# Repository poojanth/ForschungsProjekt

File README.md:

## ForschungsProjekt

KiCad PCB Design for an Implantable Optical Sensor System for Glioblastoma Cancer Patients

## Overview

This project focused on the design and optimization of a printed circuit board (PCB) for an implantable optical sensor system intended for biomedical research. The system concept is based on fluorescence detection for monitoring possible glioblastoma recurrence after tumor resection.

The implant concept consists of two main parts:

* **Sensor Unit** - responsible for fluorescence excitation and detection.
* **Control Unit** - responsible for power management, signal handling, and system control.

The aim of the project was to improve the electrical design, component selection, PCB layout, compactness, and feasibility of the optical implant system.

---

## My Contribution

* Researched requirements for implantable optical sensor systems
* Compared suitable electronic components for the device
* Investigated power management options for implantable medical devices
* Designed PCB layouts for the sensor unit and control unit using KiCad
* Considered compactness, signal integrity, power/ground planes, and routing rules
* Evaluated an alternative two-step placement approach for improved clinical feasibility

---

## Key Design Considerations

* Fluorescence excitation using UV/blue LEDs
* Fluorescence detection using photodiodes
* Compact PCB layout for implantable use
* Power-efficient component selection
* Separate power and ground planes for improved signal integrity
* MRI compatibility and biocompatibility considerations
* Sensor and control-unit separation for better placement flexibility

---

## Tools Used

* KiCad
* PCB schematic design
* PCB layout design
* Component datasheet analysis
* Literature research

---

## Skills Demonstrated

* PCB design
* Biomedical hardware design
* KiCad workflow
* Component selection
* Power management research
* Sensor system design
* Implantable medical device considerations
* Technical documentation

---

## Repository Structure

```text
.
├── KiCad_Project/
│   ├── project_file.kicad_pro
│   ├── schematic.kicad_sch
│   └── pcb_layout.kicad_pcb
│
├── Docs/
│   ├── schematic.pdf
│   ├── pcb_layout_images/
│   └── 3d_pcb_views/
│
├── README.md
└── .gitignore
```

---

## Project Status

This project represents a research and design-stage PCB development work. The PCB layout and component selection were completed as part of the research project. Experimental validation and hardware testing were identified as future work.

---

## Confidentiality Note

This repository contains only a non-confidential project overview and selected design documentation. Sensitive institutional material, unpublished restricted details, and confidential research data are not included.

---

## Author

**Poojan Thakar**
M.Sc. Medical Systems Engineering
Otto von Guericke University Magdeburg

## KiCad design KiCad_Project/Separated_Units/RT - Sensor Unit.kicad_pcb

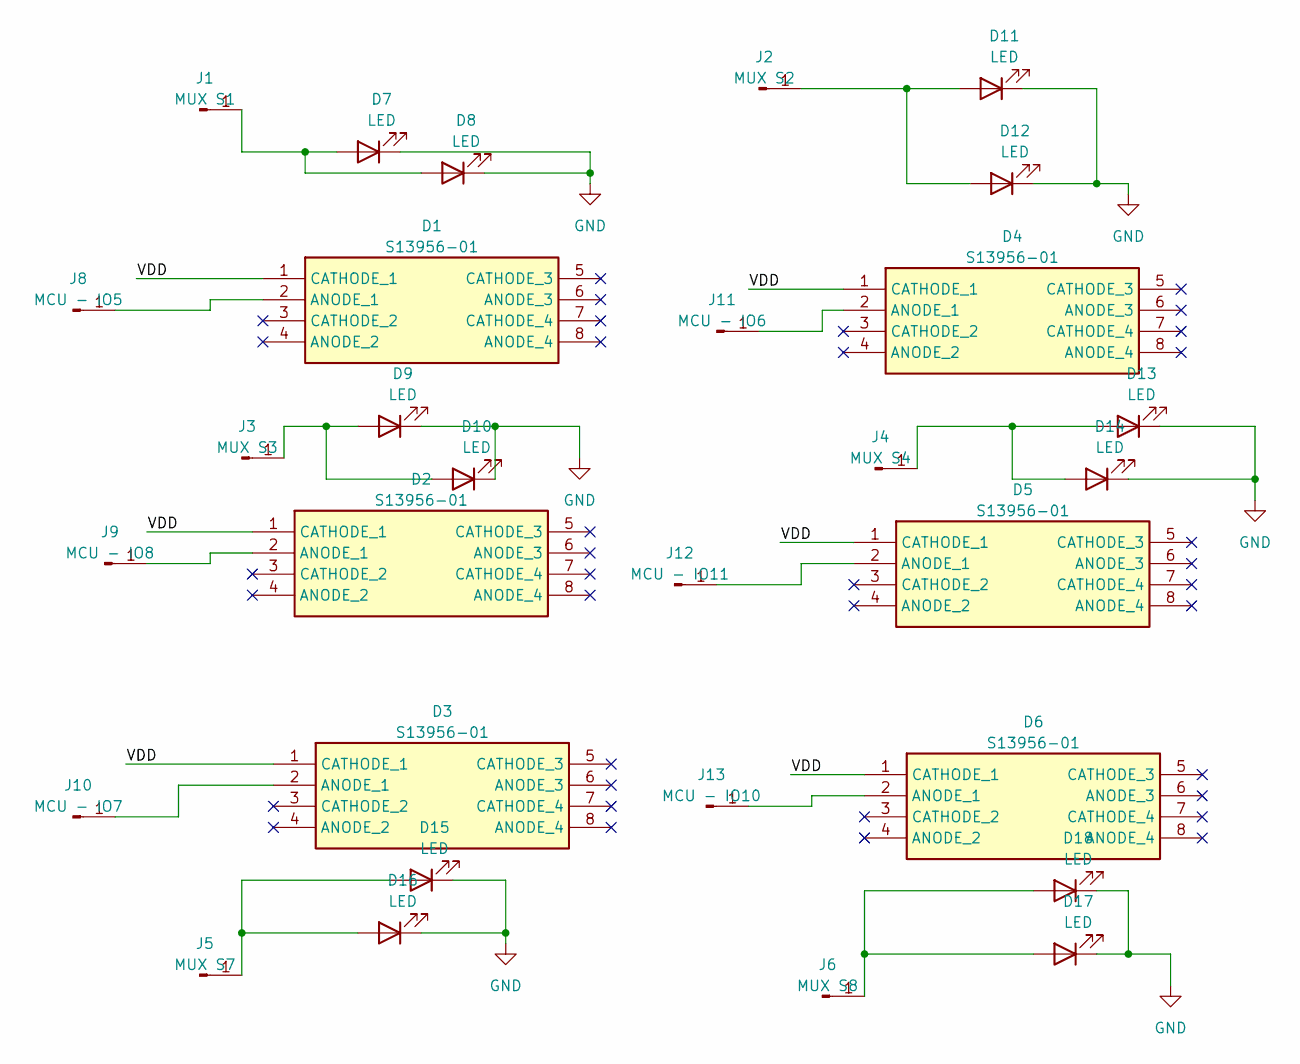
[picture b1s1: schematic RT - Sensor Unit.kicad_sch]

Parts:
D1, D2, D3, D4, D5, D6: S13956-01; S1395601; Manufacturer_Part_Number S13956-01
D7, D8, D9, D10, D11, D12, D13, D14, D15, D16, D17, D18: LED; LED_0201_0603Metric_Pad0.64x0.40mm_HandSolder
J1: MUX S1; PinHeader_1x01_P1.00mm_Vertical
J2: MUX S2; PinHeader_1x01_P1.00mm_Vertical
J3: MUX S3; PinHeader_1x01_P1.00mm_Vertical
J4: MUX S4; PinHeader_1x01_P1.00mm_Vertical
J5: MUX S7; PinHeader_1x01_P1.00mm_Vertical
J6: MUX S8; PinHeader_1x01_P1.00mm_Vertical
J8: MCU - IO5; PinHeader_1x01_P1.00mm_Vertical
J9: MCU - IO8; PinHeader_1x01_P1.00mm_Vertical
J10: MCU - IO7; PinHeader_1x01_P1.00mm_Vertical
J11: MCU - IO6; PinHeader_1x01_P1.00mm_Vertical
J12: MCU - IO11; PinHeader_1x01_P1.00mm_Vertical
J13: MCU - IO10; PinHeader_1x01_P1.00mm_Vertical

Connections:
/VDD: D1.1 (CATHODE_1), D2.1 (CATHODE_1), D3.1 (CATHODE_1), D4.1 (CATHODE_1), D5.1 (CATHODE_1), D6.1 (CATHODE_1)
GND: D7.1 (K), D8.1 (K), D9.1 (K), D10.1 (K), D11.1 (K), D12.1 (K), D13.1 (K), D14.1 (K), D15.1 (K), D16.1 (K), D17.1 (K), D18.1 (K)
unnamed: D1.2 (ANODE_1), J8.1
unnamed: D2.2 (ANODE_1), J9.1
unnamed: D3.2 (ANODE_1), J10.1
unnamed: D4.2 (ANODE_1), J11.1
unnamed: D5.2 (ANODE_1), J12.1
unnamed: D6.2 (ANODE_1), J13.1
unnamed: D7.2 (A), D8.2 (A), J1.1
unnamed: D9.2 (A), D10.2 (A), J3.1
unnamed: D11.2 (A), D12.2 (A), J2.1
unnamed: D13.2 (A), D14.2 (A), J4.1
unnamed: D15.2 (A), D16.2 (A), J5.1
unnamed: D17.2 (A), D18.2 (A), J6.1

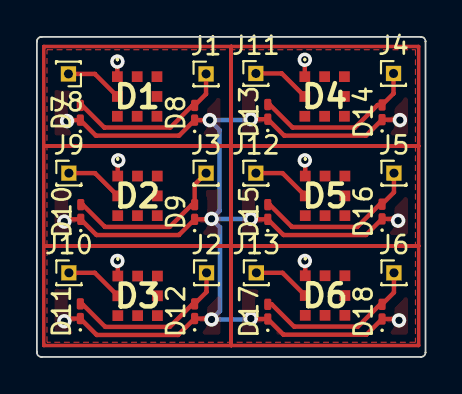
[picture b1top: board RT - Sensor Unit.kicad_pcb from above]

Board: 2 copper layers, 21.6 x 17.8 mm, 30 parts (0 on the bottom side), 14 nets.

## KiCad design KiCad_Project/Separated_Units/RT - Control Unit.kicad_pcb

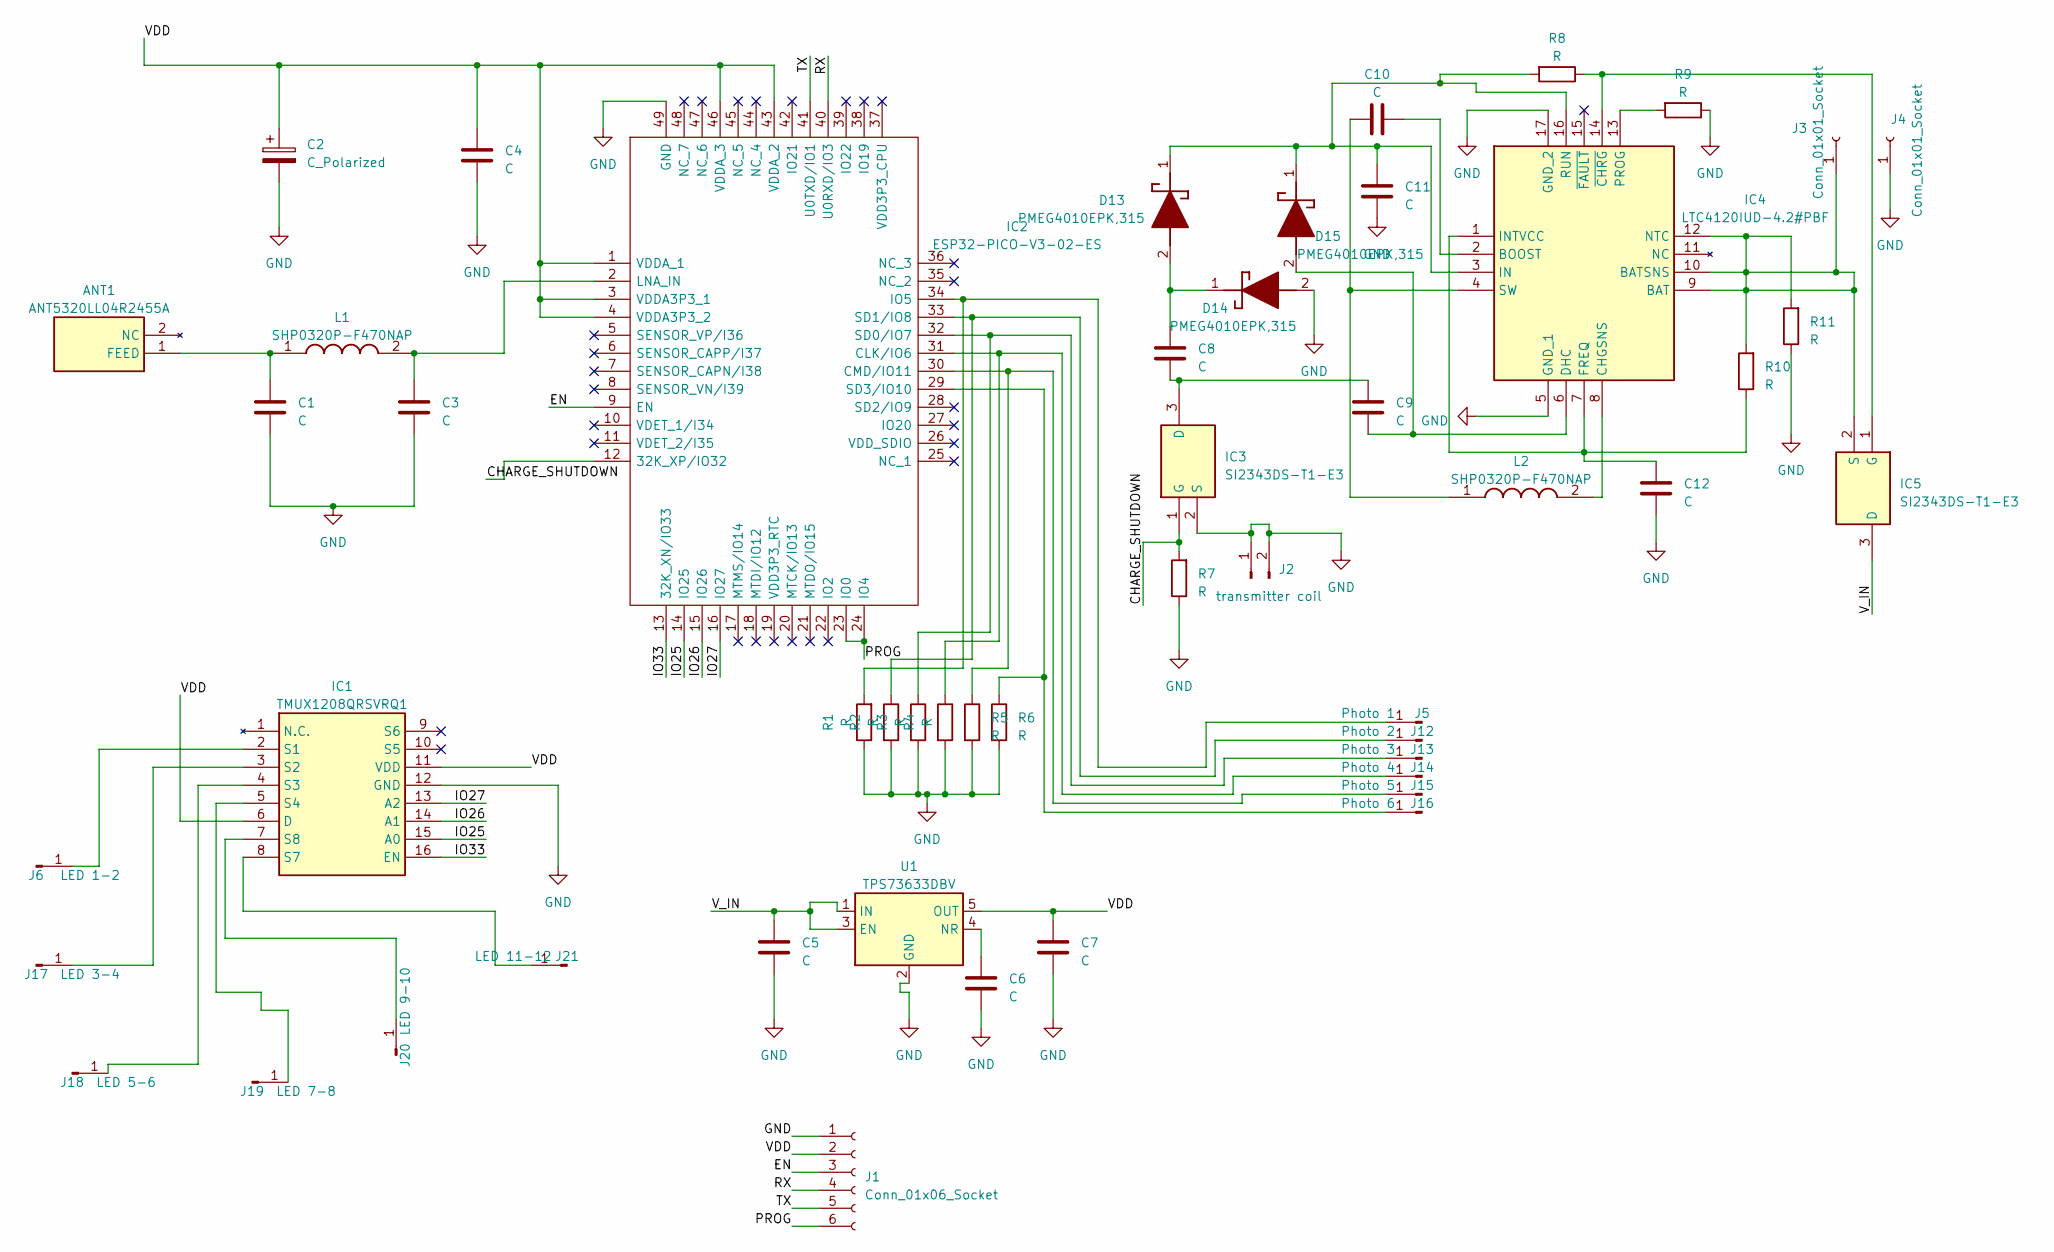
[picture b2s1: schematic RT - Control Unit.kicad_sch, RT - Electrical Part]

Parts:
ANT1: ANT5320LL04R2455A; ANTC5320X170N; Manufacturer_Part_Number ANT5320LL04R2455A; Mouser Part Number 603-ANT5320LL04R2455
C1, C3, C4, C5, C6, C7, C8, C9, C10, C11, C12: C; C_0603_1608Metric_Pad1.08x0.95mm_HandSolder
C2: C_Polarized; C_0603_1608Metric_Pad1.08x0.95mm_HandSolder
D13, D14, D15: PMEG4010EPK,315; PMEG4010EPK315; Manufacturer_Part_Number PMEG4010EPK,315; Mouser Part Number 771-PMEG4010EPK,315
IC1: TMUX1208QRSVRQ1; Manufacturer_Part_Number TMUX1208QRSVRQ1; Mouser Part Number 595-TMUX1208QRSVRQ1
IC2: ESP32-PICO-V3-02-ES; ESP32PICOV302ES; Manufacturer_Part_Number ESP32-PICO-V3-02-ES
IC3, IC5: SI2343DS-T1-E3; SOT95P237X112-3N; Manufacturer_Part_Number SI2343DS-T1-E3; Mouser Part Number 781-SI2343DS-T1-E3
IC4: LTC4120IUD-4.2#PBF; QFN50P300X300X80-17N-D; Manufacturer_Part_Number LTC4120IUD-4.2#PBF; Mouser Part Number 584-C4120IUD-4.2PBF
J1: Conn_01x06_Socket; PinHeader_2x03_P1.00mm_Vertical
J2: transmitter coil; PinHeader_1x02_P1.00mm_Vertical
J3, J4: Conn_01x01_Socket; PinHeader_1x01_P2.54mm_Vertical
J5: Photo 1; PinHeader_1x01_P1.00mm_Vertical
J6: LED 1-2; PinHeader_1x01_P1.00mm_Vertical
J12: Photo 2; PinHeader_1x01_P1.00mm_Vertical
J13: Photo 3; PinHeader_1x01_P1.00mm_Vertical
J14: Photo 4; PinHeader_1x01_P1.00mm_Vertical
J15: Photo 5; PinHeader_1x01_P1.00mm_Vertical
J16: Photo 6; PinHeader_1x01_P1.00mm_Vertical
J17: LED 3-4; PinHeader_1x01_P1.00mm_Vertical
J18: LED 5-6; PinHeader_1x01_P1.00mm_Vertical
J19: LED 7-8; PinHeader_1x01_P1.00mm_Vertical
J20: LED 9-10; PinHeader_1x01_P1.00mm_Vertical
J21: LED 11-12; PinHeader_1x01_P1.00mm_Vertical
L1, L2: SHP0320P-F470NAP; SHP0320PF470NAP; Manufacturer_Part_Number SHP0320P-F470NAP
R1, R2, R3, R4, R5, R6, R7, R8, R9, R10, R11: R; R_0402_1005Metric_Pad0.72x0.64mm_HandSolder
U1: TPS73633DBV; SOT-23-5

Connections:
/CHARGE_SHUTDOWN: IC2.12 (32K_XP/IO32), IC3.1 (G), R7.2
/EN: IC2.9 (EN), J1.3
/IO25: IC1.15 (A0), IC2.14 (IO25)
/IO26: IC1.14 (A1), IC2.15 (IO26)
/IO27: IC1.13 (A2), IC2.16 (IO27)
/IO33: IC1.16 (EN), IC2.13 (32K_XN/IO33)
/PROG: IC2.23 (IO0), IC2.24 (IO4), J1.6
/RX: IC2.40 (U0RXD/IO3), J1.4
/TX: IC2.41 (U0TXD/IO1), J1.5
/VDD: C2.1, C4.1, C7.1, IC1.6 (D), IC1.11 (VDD), IC2.1 (VDDA_1), IC2.3 (VDDA3P3_1), IC2.4 (VDDA3P3_2), IC2.43 (VDDA_2), IC2.46 (VDDA_3), J1.2, U1.5 (OUT)
/V_IN: C5.1, IC5.3 (D), U1.1 (IN), U1.3 (EN)
GND: C1.2, C2.2, C3.2, C4.2, C5.2, C6.2, C7.2, C11.2, C12.1, D14.2 (A), IC1.12 (GND), IC2.49 (GND), IC3.2 (S), IC4.5 (GND_1), IC4.17 (GND_2), J1.1, J4.1, R1.1, R2.2, R3.2, R4.2, R5.2, R6.2, R7.1, R9.1, R11.1, U1.2 (GND)
unnamed: ANT1.1 (FEED), C1.1, L1.1
unnamed: C8.1, D13.2 (A), D14.1 (K)
unnamed: C11.1, D13.1 (K), D15.1 (K), IC4.3 (IN), IC4.16 (RUN), R8.2
unnamed: C9.1, D15.2 (A), IC4.6 (DHC)
unnamed: IC1.2 (S1), J6.1
unnamed: IC1.3 (S2), J17.1
unnamed: IC1.4 (S3), J18.1
unnamed: IC1.5 (S4), J19.1
unnamed: IC1.8 (S7), J21.1
unnamed: IC1.7 (S8), J20.1
unnamed: IC2.31 (CLK/IO6), J14.1, R4.1
unnamed: IC2.30 (CMD/IO11), J15.1, R5.1
unnamed: IC2.34 (IO5), J5.1, R1.2
unnamed: C3.1, IC2.2 (LNA_IN), L1.2
unnamed: IC2.32 (SD0/IO7), J13.1, R3.1
unnamed: IC2.33 (SD1/IO8), J12.1, R2.1
unnamed: IC2.29 (SD3/IO10), J16.1, R6.1
unnamed: C8.2, C9.2, IC3.3 (D)
unnamed: IC4.9 (BAT), IC4.10 (BATSNS), IC4.12 (NTC), IC5.2 (S), J3.1, R10.2, R11.2
unnamed: C10.2, IC4.2 (BOOST)
unnamed: IC4.8 (CHGSNS), L2.2
unnamed: C12.2, IC4.1 (INTVCC), IC4.7 (FREQ), R10.1
unnamed: IC4.13 (PROG), R9.2
unnamed: C10.1, IC4.4 (SW), L2.1
unnamed: IC4.14 (~CHRG), IC5.1 (G), R8.1
unnamed: C6.1, U1.4 (NR)

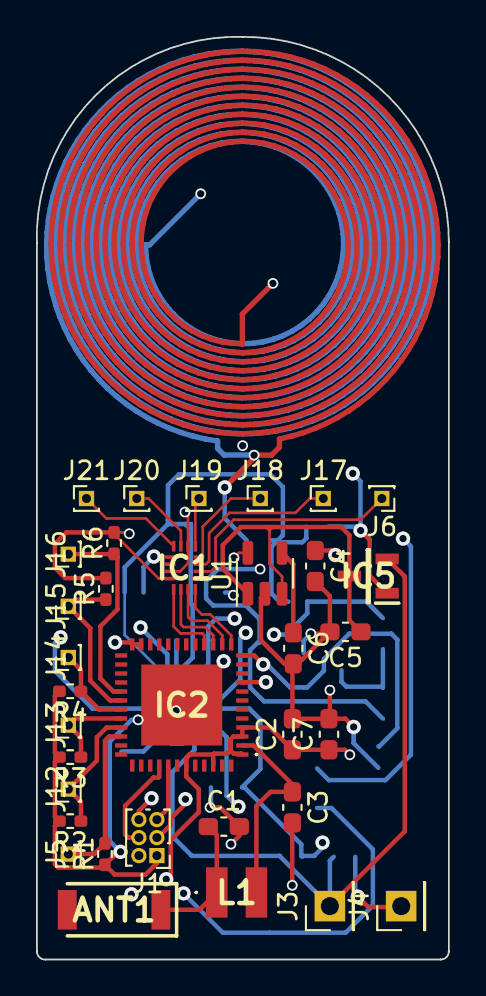
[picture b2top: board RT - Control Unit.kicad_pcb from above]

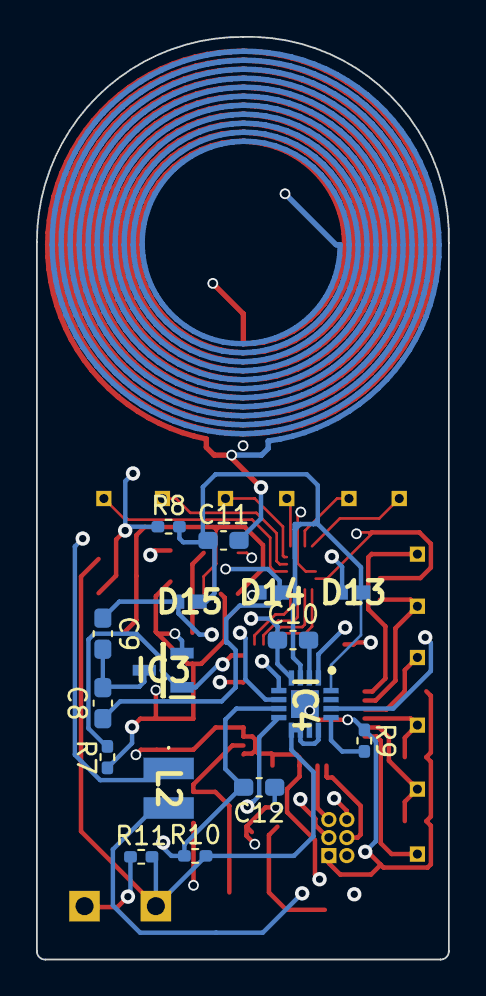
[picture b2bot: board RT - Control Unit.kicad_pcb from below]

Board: 4 copper layers, 22.9 x 51.3 mm, 50 parts (16 on the bottom side), 38 nets.

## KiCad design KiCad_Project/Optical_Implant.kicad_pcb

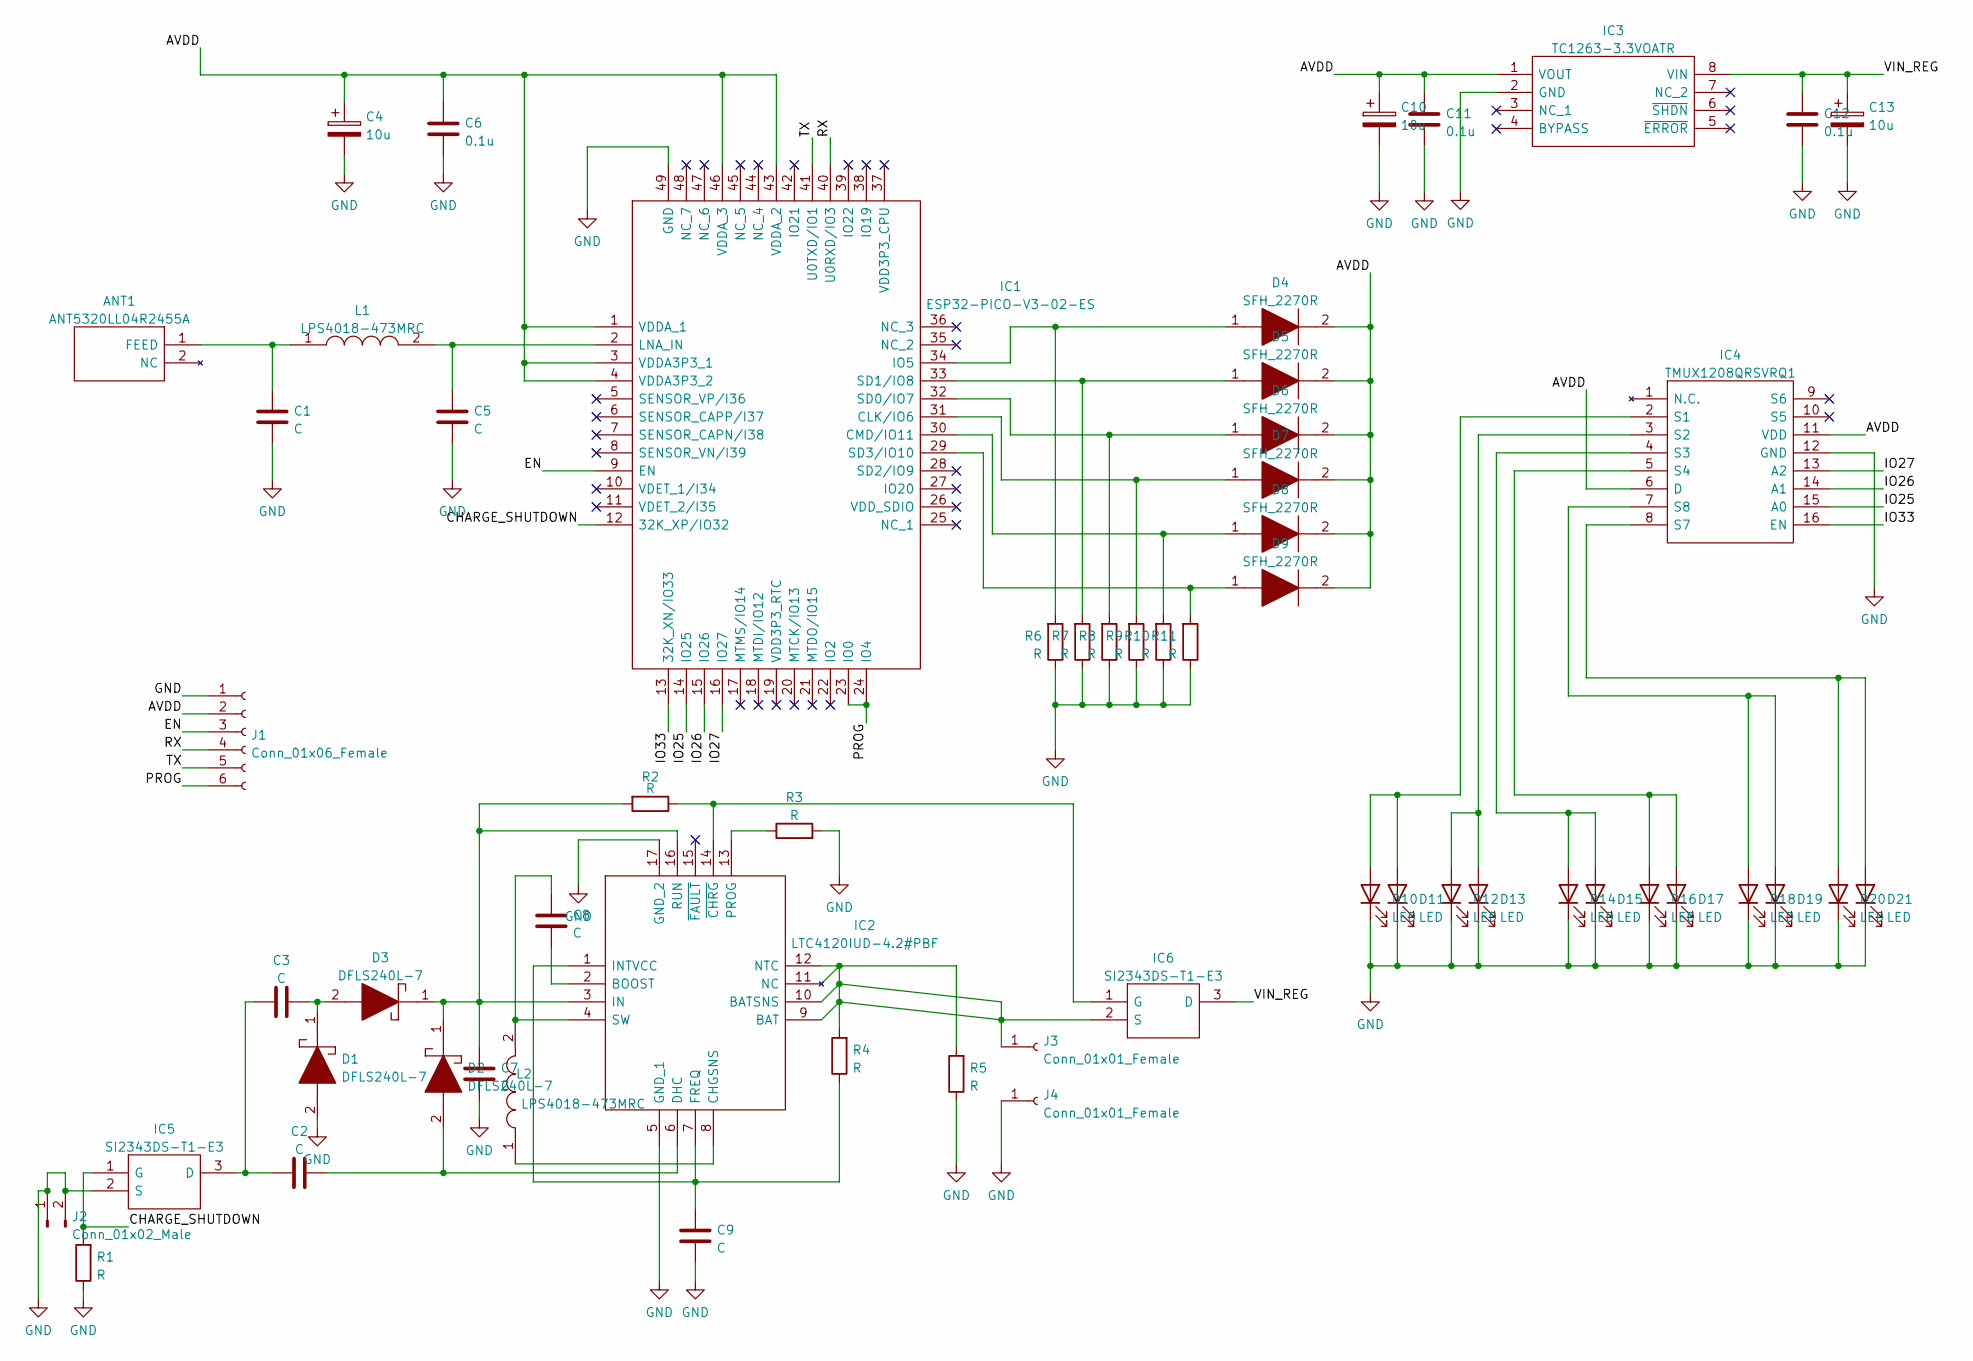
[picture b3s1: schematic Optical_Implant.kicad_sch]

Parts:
ANT1: ANT5320LL04R2455A; ANTC5320X170N; Mouser Part Number 603-ANT5320LL04R2455
C1, C2, C3, C5, C7, C8, C9: C; C_0603_1608Metric_Pad1.08x0.95mm_HandSolder
C4, C10, C13: 10u; C_0603_1608Metric_Pad1.08x0.95mm_HandSolder
C6, C11, C12: 0.1u; C_0603_1608Metric_Pad1.08x0.95mm_HandSolder
D1, D2, D3: DFLS240L-7; DFLS240L7; Manufacturer_Part_Number DFLS240L-7; Mouser Part Number 621-DFLS240L-7
D4, D5, D6, D7, D8, D9: SFH_2270R; SFH2270R; Mouser Part Number 720-SFH2270R
D10, D11, D12, D13, D14, D15, D16, D17, D18, D19, D20, D21: LED; LED_0603_1608Metric_Pad1.05x0.95mm_HandSolder
IC1: ESP32-PICO-V3-02-ES; ESP32PICOV302ES; Manufacturer_Part_Number ESP32-PICO-V3-02-ES
IC2: LTC4120IUD-4.2#PBF; QFN50P300X300X80-17N-D; Mouser Part Number 584-C4120IUD-4.2PBF
IC3: TC1263-3.3VOATR; SOIC127P600X175-8N; Mouser Part Number 579-TC1263-3.3VOATR
IC4: TMUX1208QRSVRQ1; Mouser Part Number 595-TMUX1208QRSVRQ1
IC5, IC6: SI2343DS-T1-E3; SOT95P237X112-3N; Mouser Part Number 781-SI2343DS-T1-E3
J1: Conn_01x06_Female; PinHeader_2x03_P1.00mm_Vertical
J2: Conn_01x02_Male; PinHeader_1x02_P2.54mm_Vertical
J3, J4: Conn_01x01_Female; PinHeader_1x01_P2.54mm_Vertical
L1: LPS4018-473MRC; L_0603_1608Metric_Pad1.05x0.95mm_HandSolder; Manufacturer_Part_Number LPS4018-473MRC; Mouser Part Number 994-LPS4018-473MRC
L2: LPS4018-473MRC; LPS4018473MRC; Manufacturer_Part_Number LPS4018-473MRC; Mouser Part Number 994-LPS4018-473MRC
R1, R2, R3, R4, R5, R6, R7, R8, R9, R10, R11: R; R_0402_1005Metric_Pad0.72x0.64mm_HandSolder

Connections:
/AVDD: C4.1, C6.1, C10.1, C11.1, D4.2, D5.2, D6.2, D7.2, D8.2, D9.2, IC1.1 (VDDA_1), IC1.3 (VDDA3P3_1), IC1.4 (VDDA3P3_2), IC1.43 (VDDA_2), IC1.46 (VDDA_3), IC3.1 (VOUT), IC4.6 (D), IC4.11 (VDD), J1.2
/CHARGE_SHUTDOWN: IC1.12 (32K_XP/IO32), IC5.1 (G), R1.2
/EN: IC1.9 (EN), J1.3
/IO25: IC1.14 (IO25), IC4.15 (A0)
/IO26: IC1.15 (IO26), IC4.14 (A1)
/IO27: IC1.16 (IO27), IC4.13 (A2)
/IO33: IC1.13 (32K_XN/IO33), IC4.16 (EN)
/PROG: IC1.23 (IO0), IC1.24 (IO4), J1.6
/RX: IC1.40 (U0RXD/IO3), J1.4
/TX: IC1.41 (U0TXD/IO1), J1.5
/VIN_REG: C12.1, C13.1, IC3.8 (VIN), IC6.3 (D)
GND: C1.2, C4.2, C5.2, C6.2, C7.2, C9.2, C10.2, C11.2, C12.2, C13.2, D1.2, D10.1 (K), D11.1 (K), D12.1 (K), D13.1 (K), D14.1 (K), D15.1 (K), D16.1 (K), D17.1 (K), D18.1 (K), D19.1 (K), D20.1 (K), D21.1 (K), IC1.49 (GND), IC2.5 (GND_1), IC2.17 (GND_2), IC3.2 (GND), IC4.12 (GND), IC5.2 (S), J1.1, J2.1, J2.2, J4.1, R1.1, R3.2, R5.1, R6.1, R7.1, R8.1, R9.1, R10.1, R11.1
unnamed: ANT1.1 (FEED), C1.1, L1.1
unnamed: C2.1, C3.1, IC5.3 (D)
unnamed: C2.2, D2.2, IC2.6 (DHC)
unnamed: C3.2, D1.1, D3.2
unnamed: C5.1, IC1.2 (LNA_IN), L1.2
unnamed: C7.1, D2.1, D3.1, IC2.3 (IN), IC2.16 (RUN), R2.2
unnamed: C8.1, IC2.4 (SW), L2.2
unnamed: C8.2, IC2.2 (BOOST)
unnamed: C9.1, IC2.1 (INTVCC), IC2.7 (FREQ), R4.1
unnamed: D4.1, IC1.34 (IO5), R6.2
unnamed: D5.1, IC1.33 (SD1/IO8), R7.2
unnamed: D6.1, IC1.32 (SD0/IO7), R8.2
unnamed: D7.1, IC1.31 (CLK/IO6), R9.2
unnamed: D8.1, IC1.30 (CMD/IO11), R10.2
unnamed: D9.1, IC1.29 (SD3/IO10), R11.2
unnamed: D10.2 (A), D11.2 (A), IC4.2 (S1)
unnamed: D12.2 (A), D13.2 (A), IC4.3 (S2)
unnamed: D14.2 (A), D15.2 (A), IC4.4 (S3)
unnamed: D16.2 (A), D17.2 (A), IC4.5 (S4)
unnamed: D18.2 (A), D19.2 (A), IC4.7 (S8)
unnamed: D20.2 (A), D21.2 (A), IC4.8 (S7)
unnamed: IC2.8 (CHGSNS), L2.1
unnamed: IC2.13 (PROG), R3.1
unnamed: IC2.14 (~CHRG), IC6.1 (G), R2.1

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
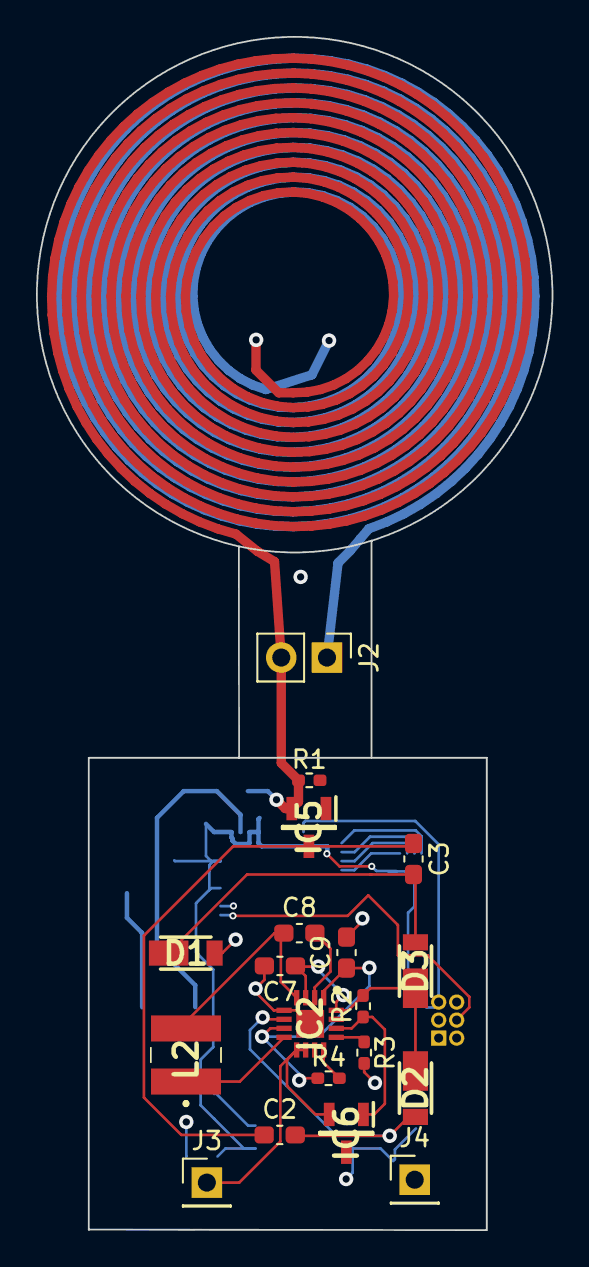
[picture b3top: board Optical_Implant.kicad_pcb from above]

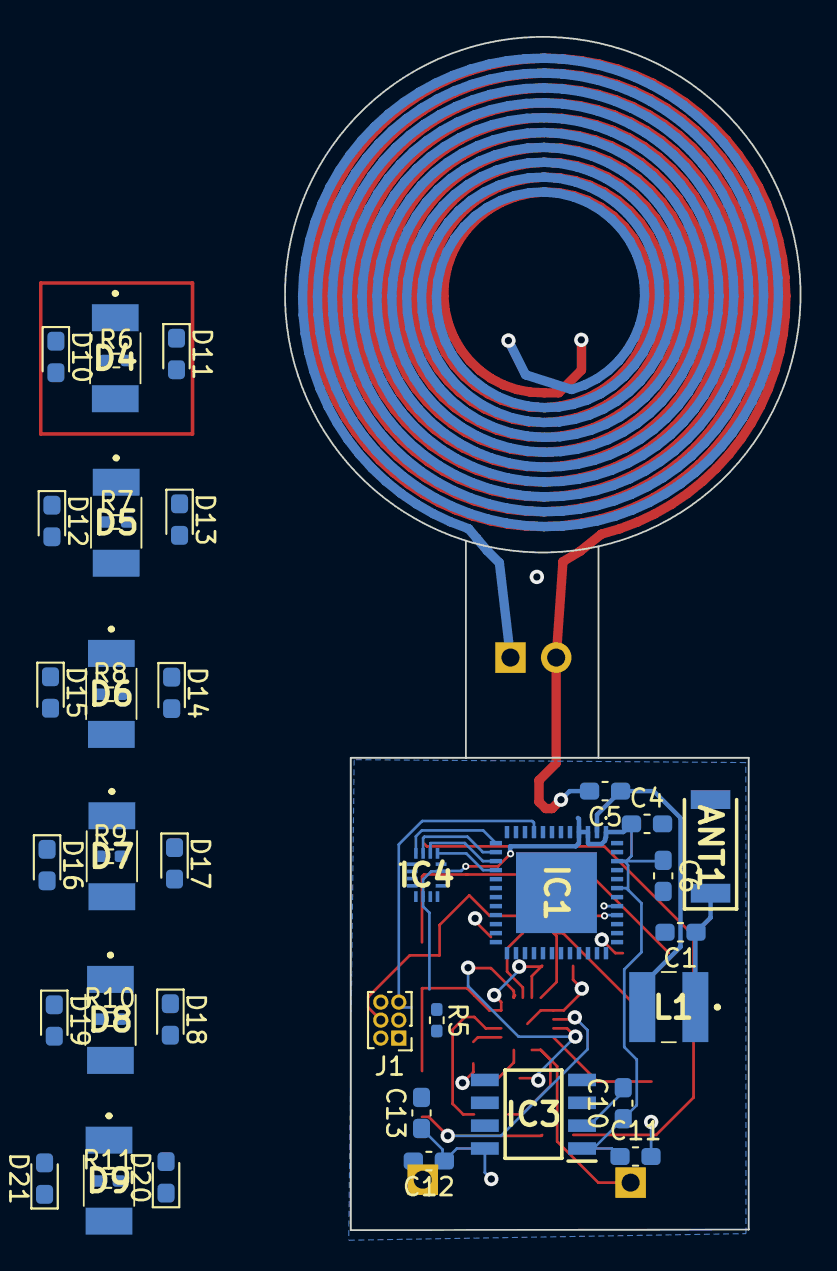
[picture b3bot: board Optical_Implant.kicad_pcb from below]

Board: 4 copper layers, 28.6 x 66.3 mm, 58 parts (39 on the bottom side), 38 nets.
